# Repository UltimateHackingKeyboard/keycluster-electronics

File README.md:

Ultimate Hacking Keyboard key cluster module
============================================

Contained are the schematics and board layout KiCad files for the [Ultimate Hacking Keyboard](https://ultimatehackingkeyboard.com/) key cluster module.

Make sure to clone this repo with:

`git clone --recursive git@github.com:UltimateHackingKeyboard/keycluster-electronics.git`

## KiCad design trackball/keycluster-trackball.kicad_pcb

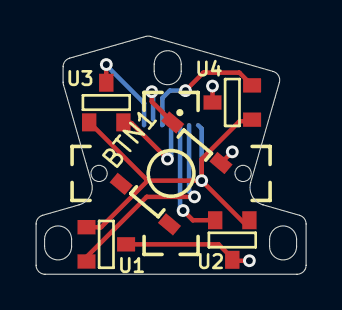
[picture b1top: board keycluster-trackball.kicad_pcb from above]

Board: 2 copper layers, 15.0 x 13.2 mm, 6 parts (1 on the bottom side), 7 nets.

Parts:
BTN1: TL3315NF100Q; TL3315NFxxxQ
P8: CONN_7; FPC_Pads_7pin_0.5mm
U1, U2, U3, U4: TLE49681MXTSA1; SOT-23

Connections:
+3V3: P8.1, U1.1, U2.1, U3.1, U4.1
/TB_BTN: BTN1.1, P8.6
/TB_DOWN: P8.3, U2.2
/TB_LEFT: P8.2, U1.2
/TB_RIGHT: P8.5, U4.2
/TB_UP: P8.4, U3.2
GND: BTN1.2, P8.7, U1.3, U2.3, U3.3, U4.3

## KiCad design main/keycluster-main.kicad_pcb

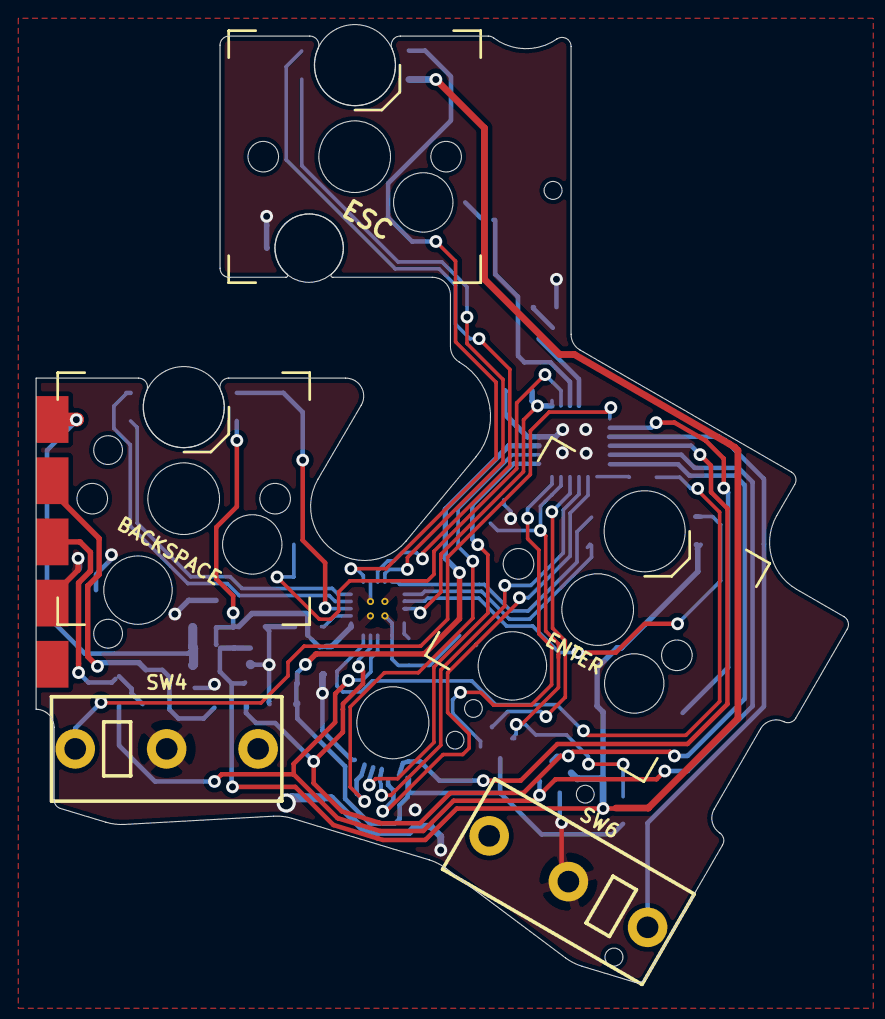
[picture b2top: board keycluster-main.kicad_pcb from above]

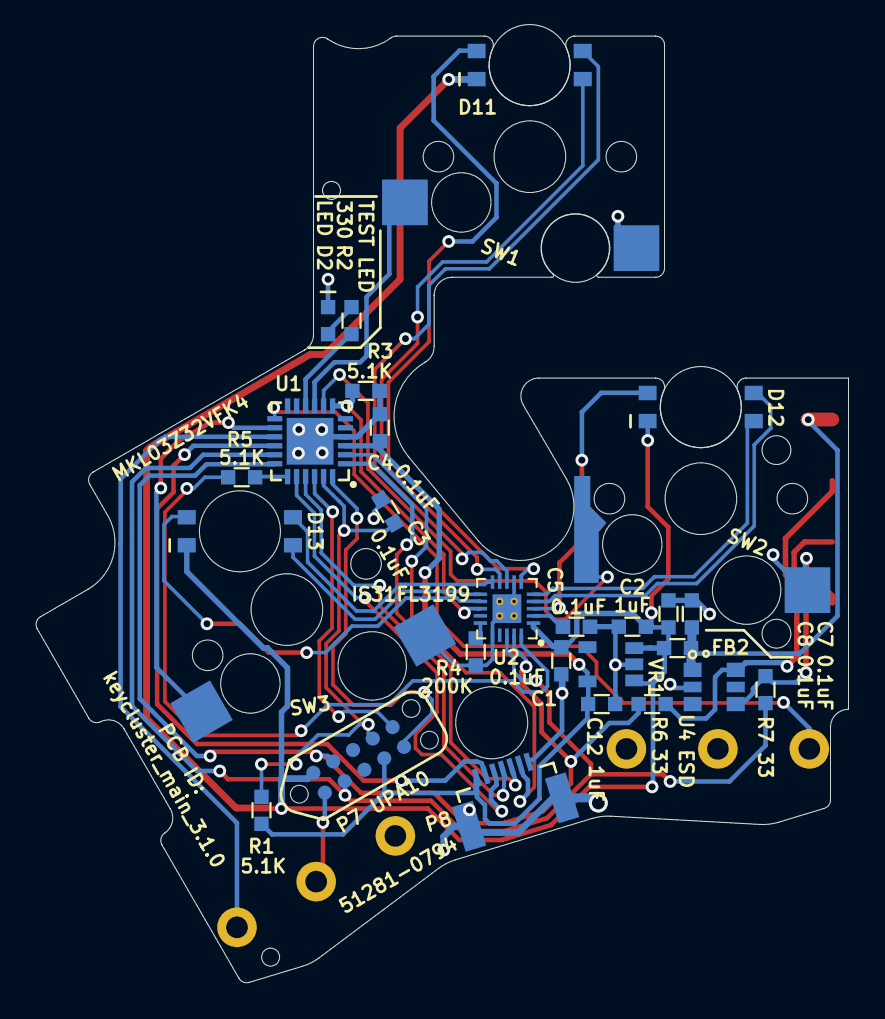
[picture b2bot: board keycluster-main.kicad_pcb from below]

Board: 2 copper layers, 45.1 x 52.6 mm, 35 parts (29 on the bottom side), 37 nets.

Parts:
C1, C3, C4, C5, C7, C8: 0.1uF; SM0603
C2, C12: 1uF; SM0603
D2: LED; SM0603_Diode
D11, D12, D13: RGB_LED
FB2: FERRITE_BEAD; SM0603
P2: CONN_5; UHK_Connector_TrackBall_Pcb
P7: CONN_10; Tag_Connect_2x5_Header_With_No_Legs_Parallel_Numbering
P8: CONN_7; FFC_Connector_51281-0794
R1, R3, R5: 5.1K; SM0603
R2: 330; SM0603
R4: 200K; SM0603
R6, R7: 33; SM0603
SW1, SW3: S01_Socket; S01_Hybrid_Socket
SW2: S01_Socket; S01_Hybrid_Socket_Backslash
SW4, SW6: CMI126603D08
U1: MKL03Z32VFK4; QFN-24-1EP_4x4mm_Pitch0.5mm
U2: IS31FL3199; QFN-20_EP_3x3_Pitch0.4mm
U4: ESD; SC-74-TVS
VR1: MIC5504-3.3YM5; SOT-23-5
hole: 1.0mm; hole_1.0mm
hole 2.2mm: VAL**; hole_4.0mm
hole#2: 1.0mm; hole_1.0mm

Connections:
+3V3: C4.2, C12.2, P7.7, P8.1, R1.1, U1.3, VR1.5
+5V: C1.2, C2.2, C8.2, D11.4, D12.4, D13.4, FB2.2, P7.2, U2.1, VR1.1, VR1.3
/CLK: R5.2, U1.19
/RESET: C3.2, P7.8, R1.2, U1.23
/SCL: P7.3, R7.1, U1.17, U2.18
/SCL_BOTTOM: P2.3, R7.2, U4.4
/SDA: P7.4, R6.1, U1.18, U2.19
/SDA_BOTTOM: P2.2, R6.2, U4.5
/SDB: R3.2, U1.7, U2.13
/SW1: SW1.1, U1.9
/SW2: SW2.1, U1.8
/SW3: SW3.1, U1.14
/SW4: SW4.1, U1.13
/SW5: P8.6, U1.2
/SW6: SW6.1, U1.15
/SWDCLK: P7.10, U1.22
/SWDIO: P7.9, U1.24
/TB_DOWN: P8.3, U1.20
/TB_LEFT: P8.2, U1.16
/TB_RIGHT: P8.5, U1.1
/TB_UP: P8.4, U1.21
/TEST_LED: R2.2, U1.10
/TEST_LED_R: D2.2, R2.1
/VCC_BOTTOM: C7.2, FB2.1, P2.1, U4.1
GND: C1.1, C2.1, C3.1, C4.1, C5.2, C7.1, C8.1, C12.1, D2.1, P2.4, P7.1, P8.7, R3.1, R4.1, SW1.2, SW2.2, SW3.2, SW4.2, SW6.2, U1.4, U1.25, U2.7, U2.16, U2.21, U4.2, VR1.2
unnamed: C5.1, U2.2
unnamed: D11.1, U2.8
unnamed: D11.2, U2.9
unnamed: D11.3, U2.6
unnamed: D12.1, U2.4
unnamed: D12.2, U2.5
unnamed: D12.3, U2.3
unnamed: D13.1, U2.10
unnamed: D13.2, U2.11
unnamed: D13.3, U2.12
unnamed: R4.2, U2.15
unnamed: R5.1, U2.20

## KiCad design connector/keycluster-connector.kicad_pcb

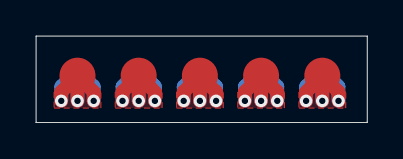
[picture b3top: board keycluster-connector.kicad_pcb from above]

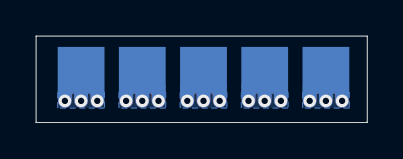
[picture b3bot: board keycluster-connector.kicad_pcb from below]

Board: 2 copper layers, 18.4 x 4.8 mm, 10 parts (5 on the bottom side), 5 nets.

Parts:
P11, P12, P13, P14, P15: CONN_1; UHK_Connector_Right_Outer_Pad
P21, P22, P23, P24, P25: CONN_1; UHK_Connector_Right_Inner_Pad

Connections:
unnamed: P11.1, P21.1
unnamed: P12.1, P22.1
unnamed: P13.1, P23.1
unnamed: P14.1, P24.1
unnamed: P15.1, P25.1

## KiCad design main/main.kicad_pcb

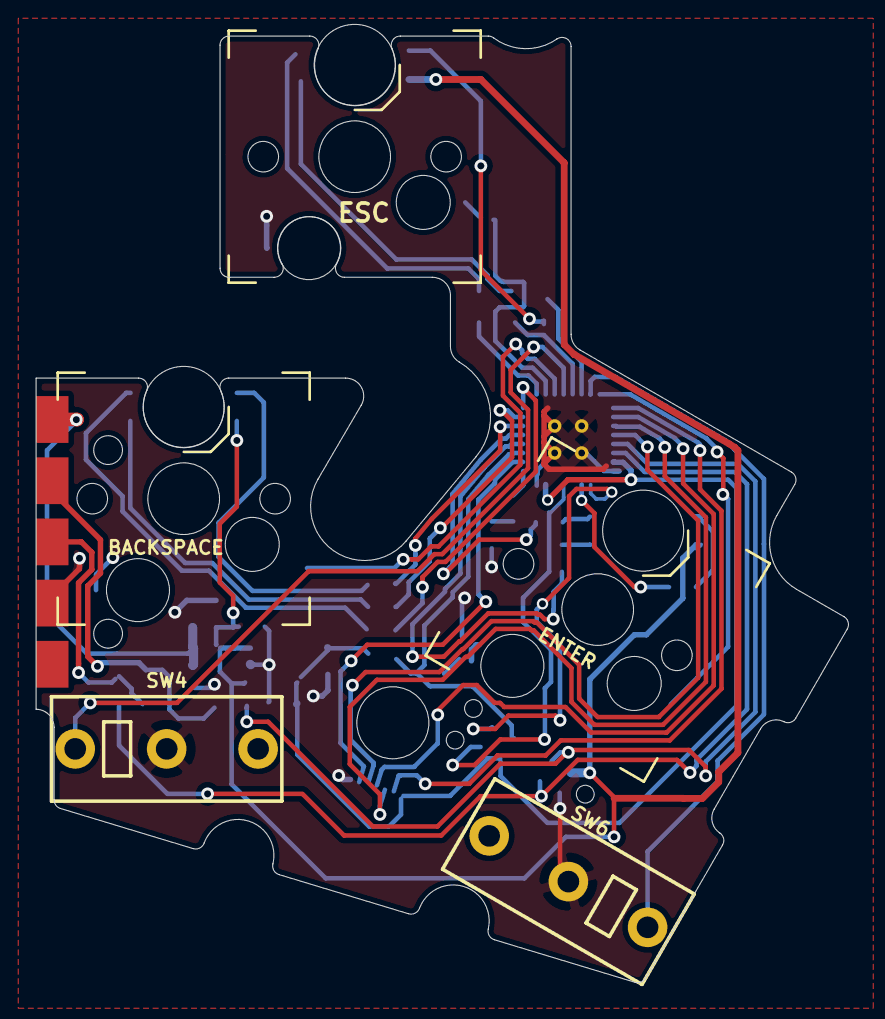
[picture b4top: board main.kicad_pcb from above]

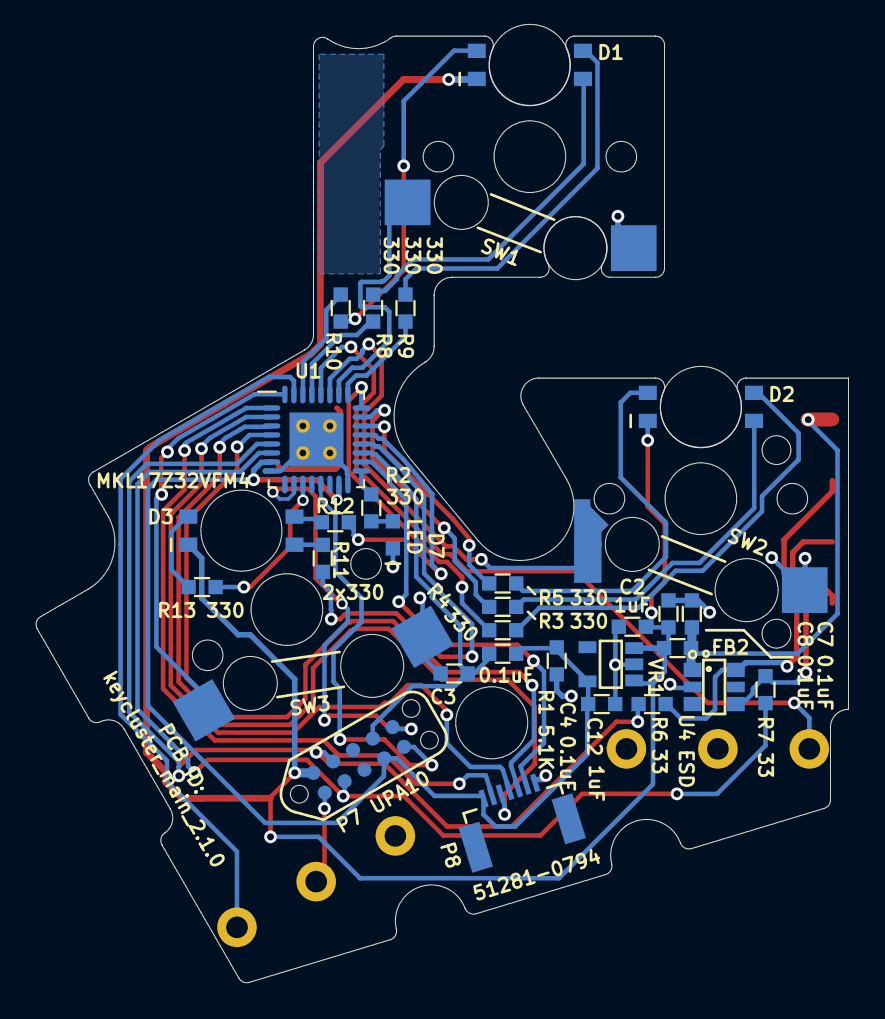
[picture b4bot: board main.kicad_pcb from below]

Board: 2 copper layers, 45.1 x 52.6 mm, 36 parts (32 on the bottom side), 41 nets.

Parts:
C2, C12: 1uF; SM0603
C3, C4, C7, C8: 0.1uF; SM0603
D1, D2, D3: RGB_LED
D7: LED; SM0603_Diode
FB2: FERRITE_BEAD; SM0603
P2: CONN_5; UHK_Connector_TrackBall_Pcb
P7: CONN_10; Tag_Connect_2x5_Header_With_No_Legs_Parallel_Numbering
P8: CONN_7; FFC_Connector_51281-0794
R1: 5.1K; SM0603
R2, R3, R4, R5, R8, R9, R10, R11, R12, R13: 330; SM0603
R6, R7: 33; SM0603
SW1, SW3: S01_Socket; S01_Hybrid_Socket
SW2: S01_Socket; S01_Hybrid_Socket_Backslash
SW4, SW6: CMI126603D08
U1: MKL17Z32VFM4; QFN-32_EP_5x5_Pitch0.5mm
U4: ESD; SC-74-TVS
VR1: MIC5504-3.3YM5; SOT-23-5
hole 2.2mm: VAL**; hole_4.0mm

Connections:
+3V3: C4.2, C12.2, P7.7, P8.1, R1.1, U1.7, U1.15, VR1.5
+5V: C2.2, C8.2, D1.4, D2.4, D3.4, FB2.2, P7.2, VR1.1, VR1.3
/RESET: C3.2, P7.8, R1.2, U1.19
/SCL: P7.3, R7.1, U1.6
/SCL_BOTTOM: P2.3, R7.2, U4.4
/SDA: P7.4, R6.1, U1.5
/SDA_BOTTOM: P2.2, R6.2, U4.5
/SW1: SW1.1, U1.26
/SW2: SW2.1, U1.27
/SW3: SW3.1, U1.32
/SW4: SW4.1, U1.28
/SW5: P8.6, U1.18
/SW6: SW6.1, U1.31
/SWDCLK: P7.10, U1.10
/SWDIO: P7.9, U1.13
/TB_DOWN: P8.3, U1.3
/TB_LEFT: P8.2, U1.1
/TB_RIGHT: P8.5, U1.4
/TB_UP: P8.4, U1.2
/TEST_LED: R2.2, U1.17
/TEST_LED_R: D7.2, R2.1
/TPM0_CH0: R5.2, U1.22
/TPM0_CH1: R3.2, U1.23
/TPM0_CH2: R4.2, U1.24
/TPM0_CH3: R9.2, U1.25
/TPM0_CH4: R8.2, U1.29
/TPM0_CH5: R10.2, U1.30
/TPM1_CH0: R11.2, U1.20
/TPM1_CH1: R12.2, U1.21
/TPM2_CH0: R13.2, U1.11
/VCC_BOTTOM: C7.2, FB2.1, P2.1, U4.1
GND: C2.1, C3.1, C4.1, C7.1, C8.1, C12.1, D7.1, P2.4, P7.1, P8.7, SW1.2, SW2.2, SW3.2, SW4.2, SW6.2, U1.8, U1.16, U1.33, U4.2, VR1.2
unnamed: D1.1, R9.1
unnamed: D1.2, R8.1
unnamed: D1.3, R10.1
unnamed: D2.1, R4.1
unnamed: D2.2, R3.1
unnamed: D2.3, R5.1
unnamed: D3.1, R12.1
unnamed: D3.2, R11.1
unnamed: D3.3, R13.1

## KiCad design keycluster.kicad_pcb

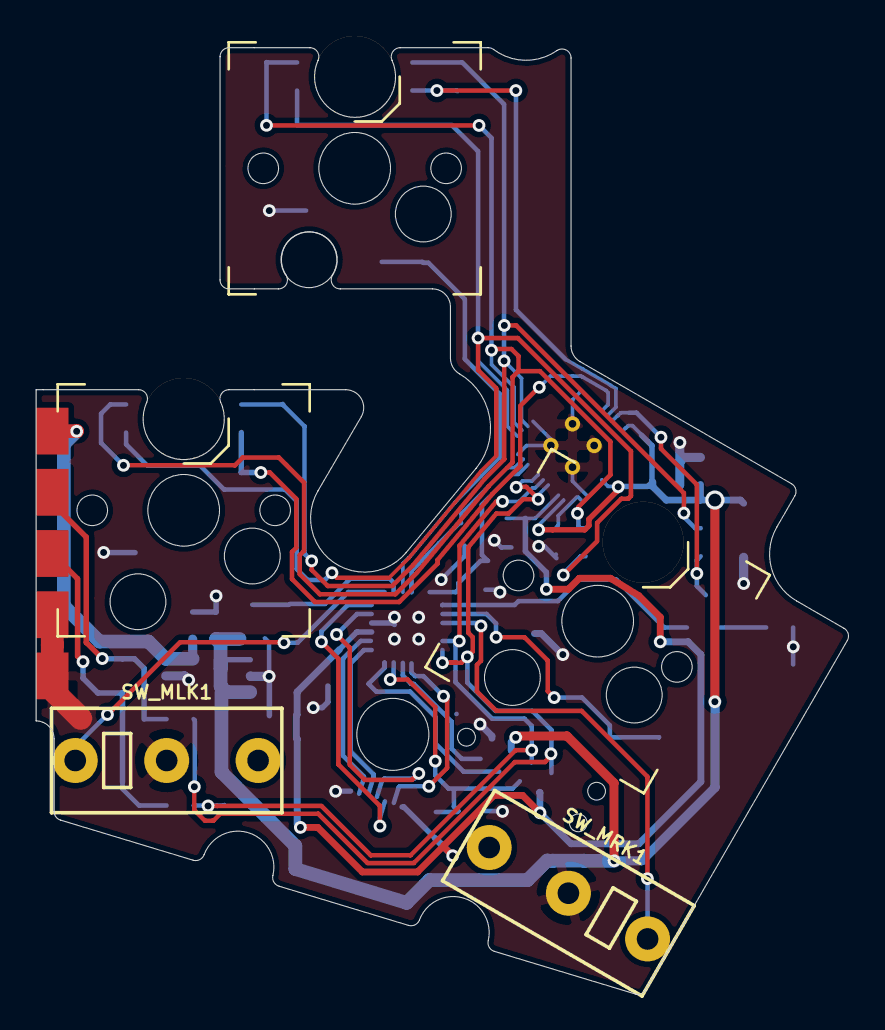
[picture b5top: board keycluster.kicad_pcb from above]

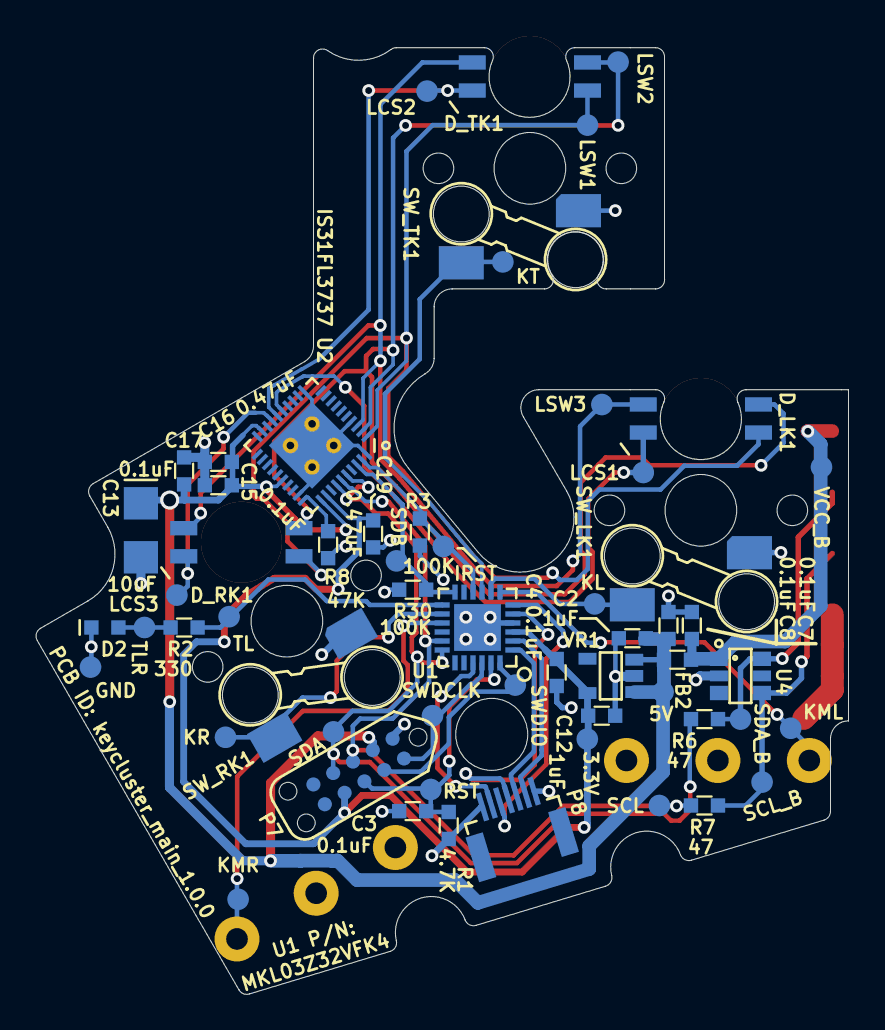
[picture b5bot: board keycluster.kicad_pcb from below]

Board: 2 copper layers, 45.1 x 52.6 mm, 62 parts (52 on the bottom side), 32 nets.

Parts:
C2, C12: 1uF; SM0603
C3, C4, C7, C8, C15, C17: 0.1uF; SM0603
C13: 10uF; SM1206_Diode
C16, C19: 0.47uF; SM0603
D2: LED; SM0603_Diode
D_LK1: RGB_LED
D_RK1: RGB_LED
D_TK1: ugl:RGB_LED; RGB_LED
FB2: FERRITE_BEAD; SM0603
P2: CONN_5; UHK_Connector_TrackBall_Pcb
P7: CONN_10; Tag_Connect_2x5_Header_With_No_Legs
P8: CONN_7; FFC_Connector_51281-0794
R1: 4.7K; SM0603
R2: 330; SM0603
R3, R30: 100K; SM0603
R6, R7: 47; SM0603
R8: 47K; SM0603
SW_LK1: LK; S01_Hybrid_Socket
SW_MLK1: MLK; CMI126603D08
SW_MRK1: MRK; CMI126603D08
SW_RK1: RK; S01_Hybrid_Socket
SW_TK1: TK; S01_Hybrid_Socket
TP_3.3V1: 3.3V; Test_Point
TP_5V1: 5V; Test_Point
TP_CS1: LCS1; Test_Point
TP_CS2: LCS2; Test_Point
TP_CS3: LCS3; Test_Point
TP_GND1: GND; Test_Point
TP_IICRST1: IRST; Test_Point
TP_KEY_LEFT1: KL; Test_Point
TP_KEY_MLEFT1: KML; Test_Point
TP_KEY_MRIGHT1: KMR; Test_Point
TP_KEY_RIGHT1: KR; Test_Point
TP_KEY_TOP1: KT; Test_Point
TP_RESET1: RST; Test_Point
TP_SCL1: SCL; Test_Point
TP_SCL_BOTTOM1: SCL_B; Test_Point
TP_SDA1: SDA; Test_Point
TP_SDA_BOTTOM1: SDA_B; Test_Point
TP_SDB1: SDB; Test_Point
TP_SW1: LSW1; Test_Point
TP_SW2: LSW2; Test_Point
TP_SW3: LSW3; Test_Point
TP_SWDCLK1: SWDCLK; Test_Point
TP_SWDIO1: SWDIO; Test_Point
TP_TEST_LED1: TL; Test_Point
TP_TEST_LED_R1: TLR; Test_Point
TP_VCC_BOTTOM1: VCC_B; Test_Point
U1: MKL03Z32VFK4; QFN-24-1EP_4x4mm_Pitch0.5mm
U2: IS31FL3737; QFN-40_EP_5x5_Pitch0.4mm
U4: ESD; SC-74-TVS
VR1: MIC5504-3.3YM5; SOT-23-5
hole 2.2mm: VAL**; hole_4.0mm

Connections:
+3V3: C4.2, C12.2, C19.1, P7.7, P8.1, R1.1, TP_3.3V1.1, U1.3, U2.32, VR1.5
+5V: C2.2, C8.2, C13.1, C15.1, C16.1, C17.1, FB2.2, P7.2, TP_5V1.1, U2.19, U2.26, U2.31, VR1.1, VR1.3
/ADDR: P7.4, R6.1, TP_SDA1.1, U1.18, U2.34, U2.36
/IICRST: R3.1, TP_IICRST1.1, U1.10, U2.39
/KEY_LEFT: SW_LK1.1, TP_KEY_LEFT1.1, U1.8
/KEY_MLEFT: SW_MLK1.1, TP_KEY_MLEFT1.1, U1.7
/KEY_MRIGHT: SW_MRK1.1, TP_KEY_MRIGHT1.1, U1.15
/KEY_RIGHT: SW_RK1.1, TP_KEY_RIGHT1.1, U1.14
/KEY_TOP: SW_TK1.1, TP_KEY_TOP1.1, U1.9
/LED_CS1: D_LK1.4, TP_CS1.1, U2.15
/LED_CS2: D_TK1.4, TP_CS2.1, U2.16
/LED_CS3: D_RK1.4, TP_CS3.1, U2.17
/LED_SW1: D_LK1.2, D_RK1.2, D_TK1.2, TP_SW1.1, U2.1
/LED_SW2: D_LK1.1, D_RK1.1, D_TK1.1, TP_SW2.1, U2.2
/LED_SW3: D_LK1.3, D_RK1.3, D_TK1.3, TP_SW3.1, U2.3
/RESET: C3.2, P7.8, R1.2, TP_RESET1.1, U1.23
/R_EXT: R8.1, U2.30
/SCL: P7.3, R7.1, TP_SCL1.1, U1.17, U2.35
/SCL_BOTTOM: P2.3, R7.2, TP_SCL_BOTTOM1.1, U4.4
/SDA_BOTTOM: P2.2, R6.2, TP_SDA_BOTTOM1.1, U4.5
/SDB: R30.2, TP_SDB1.1, U1.12, U2.38
/SWDCLK: P7.10, TP_SWDCLK1.1, U1.22
/SWDIO: P7.9, TP_SWDIO1.1, U1.24
/TB_BTN: P8.6, U1.2
/TB_DOWN: P8.3, U1.6
/TB_LEFT: P8.2, U1.21
/TB_RIGHT: P8.5, U1.1
/TB_UP: P8.4, U1.5
/TEST_LED: R2.2, TP_TEST_LED1.1, U1.13
/TEST_LED_R: D2.2, R2.1, TP_TEST_LED_R1.1
/VCC_BOTTOM: C7.2, FB2.1, P2.1, TP_VCC_BOTTOM1.1, U4.1
GND: C2.1, C3.1, C4.1, C7.1, C8.1, C12.1, C13.2, C15.2, C16.2, C17.2, C19.2, D2.1, P2.4, P2.5, P7.1, P8.7, R3.2, R8.2, R30.1, SW_LK1.2, SW_MLK1.2, SW_MRK1.2, SW_RK1.2, SW_TK1.2, TP_GND1.1, U1.4, U1.25, U2.4, U2.11, U2.29, U2.40, U2.41, U4.2, VR1.2

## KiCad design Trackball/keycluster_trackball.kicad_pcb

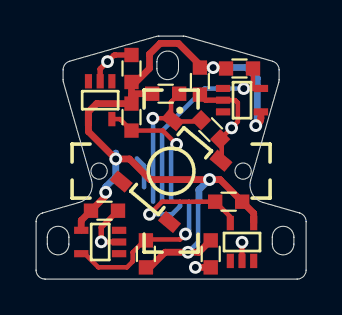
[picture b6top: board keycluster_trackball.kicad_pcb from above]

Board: 2 copper layers, 15.0 x 13.5 mm, 16 parts (1 on the bottom side), 7 nets.

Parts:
BTN1: BTN; TL3315NF250Q
C1, C2, C3, C4, C5: 0.1uF; SM0603
P8: CONN_7; FFC_Connector_51281-0794
R1, R2, R3, R4, R5: 10K; SM0603
U1, U2, U3, U4: AN48841B; SMINI-5DE

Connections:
+3V3: C1.2, C2.2, C3.2, C4.2, P8.1, R1.1, R2.1, R3.1, R4.1, R5.1, U1.4, U2.4, U3.4, U4.4
/TB_BTN: BTN1.1, C5.2, P8.6, R5.2
/TB_DOWN: P8.3, R2.2, U2.5
/TB_LEFT: P8.2, R1.2, U1.5
/TB_RIGHT: P8.5, R4.2, U4.5
/TB_UP: P8.4, R3.2, U3.5
GND: BTN1.2, C1.1, C2.1, C3.1, C4.1, C5.1, P8.7, U1.2, U2.2, U3.2, U4.2

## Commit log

2019-05-13 Add libs. as submodules.
2019-05-13 PCB added with mechanical layers.
2019-05-21 Libs removed and added as project specific libraries.
2019-05-21 Vertical and trackball pcb.
2019-05-27 Add version numbers on the silk screen.
2019-06-06 Keycluster project files added.
2019-06-06 Keycluster sch. page settings.
2019-06-06 Button positions changed on uC.
2019-06-06 Wiring on main pcb.
2019-06-11 Reed removed. Legless tag connector.
2019-06-20 Wiring on main pcb and 7pin FFC added.
2019-06-25 First final version pcb of main board.
2019-06-25 Improved schematic layout.
2019-06-25 Modified varsion number on main board. 0.1.0 -> 1.0.0
2019-06-25 Trackball project added. First final version of this board.
2019-06-25 Designators layer changed. tslk -> bslk
2019-06-26 Vertical pcb.
2019-07-02 Add updated vertical PCB and delete the old, incorrect one.
2019-07-03 Gitignore the gerbers directory.
2019-07-03 Rename the Trackball directory to lowercase trackball.
2019-07-03 Rename keycluster_trackball.* to trackball.* and fix trackball schematics library path.
2019-07-03 Fix sym-lib-table and add kiibohd submodule.
2019-07-03 Make board outline continuously connected.
2019-07-03 Update key cluster contour.
2019-07-03 Update soft keepout areas.
2019-07-07 Improve silk screen.
2019-07-07 Show silk screen values.
2019-07-07 Update buttons.
2019-07-07 Move main board to the new main directory.
2019-07-07 Rename keycluster.* files to main.*
2019-07-07 Fix symbol and module library paths.
2019-07-07 Spruce up the silk screen.
2019-07-07 Update description.
2019-07-07 Reduce copper pour.
2019-07-15 Add libs readme.
2019-07-17 Change hall sensor on trackball.
2019-07-17 Change UPA header pinout.
2019-07-21 Update microswitch footprint.
2019-08-06 Update contour based on CAD.
2019-08-06 Ignore generated BOM files.
2019-08-06 Update keepout areas based on CAD.
2019-08-06 Fix outline to be continuous.
2019-08-06 Remove inner edge layer artifacts and refill ground.
2019-08-06 Spruce up silk screen.
2019-08-06 Assign the same value to microswitches so that they'll be featured in a single BOM line.
2019-08-06 Assign the same value to RGB LEDs.
2019-08-06 Assign the same value to S01 sockets.
2019-08-06 Feature RGB LEDs on the correct side.
2019-08-07 Update sockets and put them on the back side.
2019-08-07 Reference the latest UGL lib.
2019-08-07 Add UHK logo.
2019-08-09 Bump board version number to 1.1.0
2019-08-09 Add UPA14 text.
2019-08-09 Update the FFC connector of the main board.
2019-08-09 Fix the module library path and update the FFC connector of the trackball board.
2019-08-10 Rename UPA14 to UPA10.
2019-08-12 Update LEDs.
2019-08-15 New contour and update library reference.
2019-08-15 Inrease contour width (custom edge.cuts clearance).
2019-08-15 Reduce Edge.Cuts line thickness to 0.01 mm.
2019-08-15 Update switch and hole footprints.
2019-08-16 Make pogo pin through hole and make logo virtual.
2019-08-16 Make the values of RGB LEDs "RGB LED".
2019-08-21 Update library reference.
2019-08-21 Change hall sensor and remove pull-up resistors.
2019-08-21 Fix outline.
2019-08-21 Resolve 1 DRC error. 2 to go.
2019-08-21 Move top edge upward by 0.3 mm. Resolve DRC issues.
2019-08-21 Move FFC connector upwards by 2 mm.
2019-08-21 Fix the angle of C5.
2019-08-21 Make layers visible.
2019-08-21 Move version number.
2019-08-21 Leave more space at the bottom of the board.
2019-08-22 Place tracks farther from the edges.
2019-08-22 Put copper farther from edges.
2019-08-22 Put copper 0.25+ mm from edges.
2019-09-25 Fix schematic dependencies, so every component renders properly.
2019-10-27 Update microswitch modules.
2019-10-27 Update LED module.
2019-10-27 Update pogo pin module and reroute board around it.
2019-10-27 Update SMD RGB LEDs.
2019-10-27 Bump version number to 1.2.0
2019-10-27 Ignore *.sch-bak
2019-10-27 Remove excess resistor and capacitor.
2019-10-27 Bump trackball version number to 1.1.0
2019-10-27 Enable front copper layer.
2020-01-11 Update schematic and board design with new uC. Remove LED driver.
2020-01-12 Wiring on board.
2020-01-13 Final wiring.
2020-01-13 Silkscreen arrangement.
2020-01-24 Make the test LED and its resistor virtual.
2020-02-07 Redesign panel with TLE4964.
2020-02-07 Improve the silk screen of the main board.
2020-02-07 Bump the version number of both boards to 2.0.0
2020-03-05 Add license.
2020-03-14 Specify gerbers directory.
2020-03-14 Remove unneeded capacitor.
2020-03-14 Update contour to rigid-flex.
2020-03-14 Add most FPC tracks.
2020-03-14 Fix switch position and orientation.
2020-03-14 Slightly tidy up routing.
2020-03-14 Change FFC connector footprint to FPC pads.
2020-03-14 Update FPC pads.
2020-03-14 Add dimensioning lines.
2020-03-14 Bump version number to 2.1.0
2020-03-14 Display PCB ID on the back of the PCB.
2020-03-14 Change plotting settings.
2020-03-14 Update SW_TK1 socket.
2020-03-14 Update SW_RK1 socket.
2020-03-14 Update SW_LK1 socket.
2020-03-14 Tidy up silk screen.
2020-03-14 Bump version to 2.1.0
2020-03-14 Lock footprints.
2020-03-14 Don't put paste on FPC pads.
2020-03-16 Update board contour based on CAD.
2020-03-17 Subtract soldermask from silk screen.
2020-03-17 Add labels for keys.
2020-03-17 Reposition right microswitch label.
2020-04-05 Disconnect the bottom pin of the pogo pin connector.
2020-04-05 Use consistent label font size.
2020-05-16 Add readme.
2020-05-17 Change parts from 4.7K to 5.1K and from 47 ohm to 33 ohm.
2020-05-20 Reposition and update FPC solder pads.
2020-05-20 Remove PCB tail.
2020-05-21 Clone trackpoint FPC here. To be modified soon.
2020-05-21 Add incomplete key cluster FPC.
2020-05-21 Add holes and soldermask.
2020-05-21 Add missing FPC features and close the outline.
2020-05-21 Add top tracks.
2020-05-21 Increase bottom mask area for better solerability.
2020-05-21 Tweak silk screen positioning.
2020-05-21 Don't use Protel gerber extensions.
2020-06-03 Update board based on CAD.
2020-06-03 Make UGL library name uppercase.
2020-06-06 Move parts away from SW_MRK1 to ease hand its soldering.
2020-06-06 Optimize routing.
2020-06-06 Move components away from SW_MLK1 for easier solderability.
2020-06-06 Simplify switch naming to SW1-SW6.
2020-06-06 Clean up silk screen.
2020-06-06 Bump version to 2.2.0
2020-06-10 Capitalize UGL library name.
2020-06-11 Rename main* to keycluster-main*
2020-06-11 Rename trackball* to keycluster-trackball*
2020-06-11 Set plot parameters.
2020-06-11 Set plotting parameters.
2020-06-11 Tweak plot settings.
2020-06-11 Rename directory to gerbers.
2020-06-11 Remove connector* to keycluster-connector*
2020-06-11 Rename filename references to keycluster-connector
2020-06-11 Update plot parameters.
2020-06-11 Tweak plot parameters.
2020-06-19 Reduce FPC length by 3 mm.
2020-06-19 Update stiffener marking.
2020-06-19 Update stiffener marker position.
2020-06-19 Increase key cluster silk screen text and shorten it to be manufacturable.
2020-06-19 Bump FPC version to 1.1.0
2020-06-22 Set socket attributes to SMD.
2020-08-03 Update QFN-32_EP_5x5_Pitch0.5mm.kicad_mod to fix center pad paste.
2020-08-04 Update socket modules.
2020-08-04 Set up clearance so that part of the logo is not covered by the soldermask around the nearby hole.
2020-08-04 Update sockets to not feature silk screen between their holes.
2020-08-04 Bump main board version to 2.3.0
2020-09-18 Bump trackball version to 2.2.0
2020-09-22 Move the FFC connector by about 0.8 mm away from the edge of the main board.
2020-09-25 Update FPC contour.
2020-09-25 Add FPC tracks and bump version to 2.0.0
2020-09-25 Reposition FPC solder pads and bump version to 2.3.0
2020-09-25 Add guiding silk screen lines to ease FPC soldering.
2020-09-26 Bump main board version to 2.4.0
2020-09-30 Fix hall sensor part name.
2020-09-30 Replace the TL3315NF250Q module with TL3315NFxxxQ and use TL3315NF100Q as the part value to describe the actual part name.
2020-10-27 Change controller and LED driver on schematic.
2020-10-27 Update PCB with new components.
2020-10-27 Routing.
2020-10-27 Reallocate control pins on schematic and routing on PCB.
2020-10-27 Completed routing.
2020-10-28 Arrange silkscreen components.
2020-10-28 Fix LED driver supply connect.
2020-10-28 Readd positioning holes.
2020-10-28 Add back UHK logo.
2020-10-29 Update the resistor values around the LED driver.
2020-10-29 Update netlist and board.
2020-10-29 Rename the test LED reference designator to D2.
2020-10-29 Add test LED section.
2020-10-29 Update VR1 and U4 silk screen.
2020-10-29 Tweak silk screen position.
2020-10-29 Bump version to 3.0.0
2020-10-29 Update U2 polarization mark.
2020-12-04 Connect IS31FL3199 to 5V instead of 3.3V
2020-12-04 Set R_EXT to 200K.
2020-12-04 Bump version to 3.1.0
2021-02-04 Set the microswitch of the trackball board to SMD instead of through-hole.
2021-11-15 Update submodule URL.
